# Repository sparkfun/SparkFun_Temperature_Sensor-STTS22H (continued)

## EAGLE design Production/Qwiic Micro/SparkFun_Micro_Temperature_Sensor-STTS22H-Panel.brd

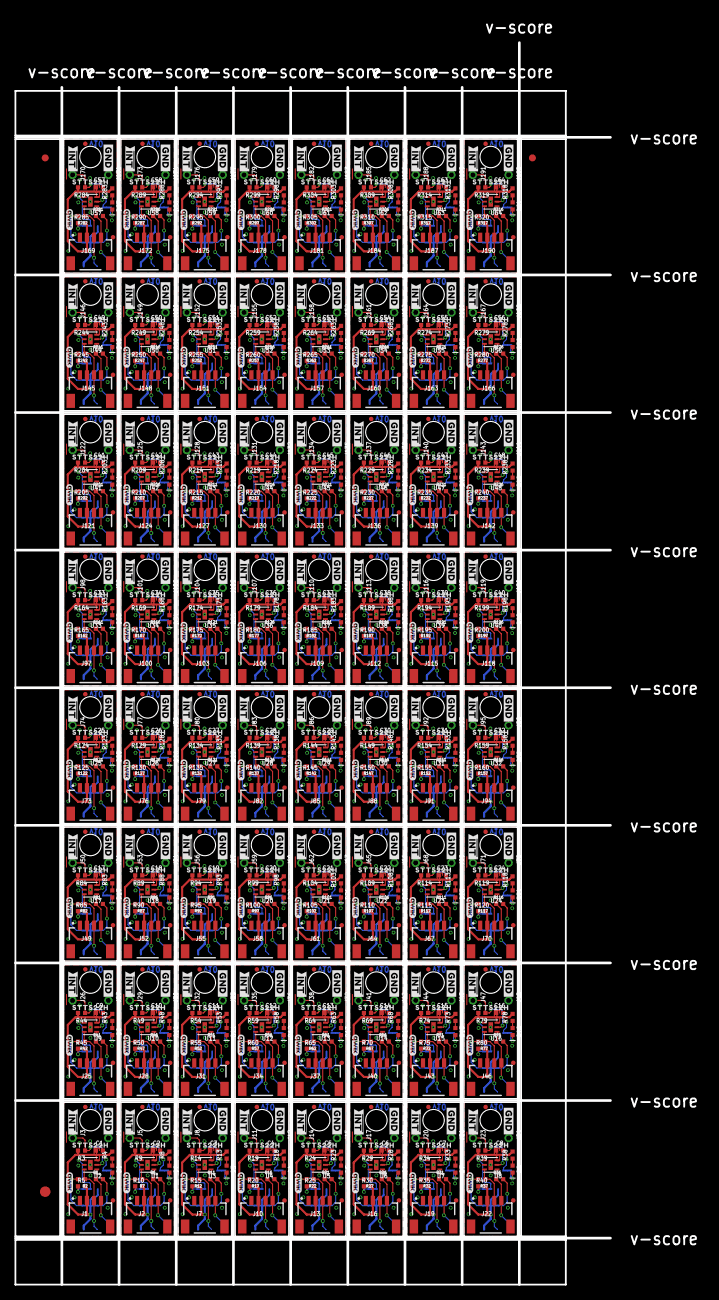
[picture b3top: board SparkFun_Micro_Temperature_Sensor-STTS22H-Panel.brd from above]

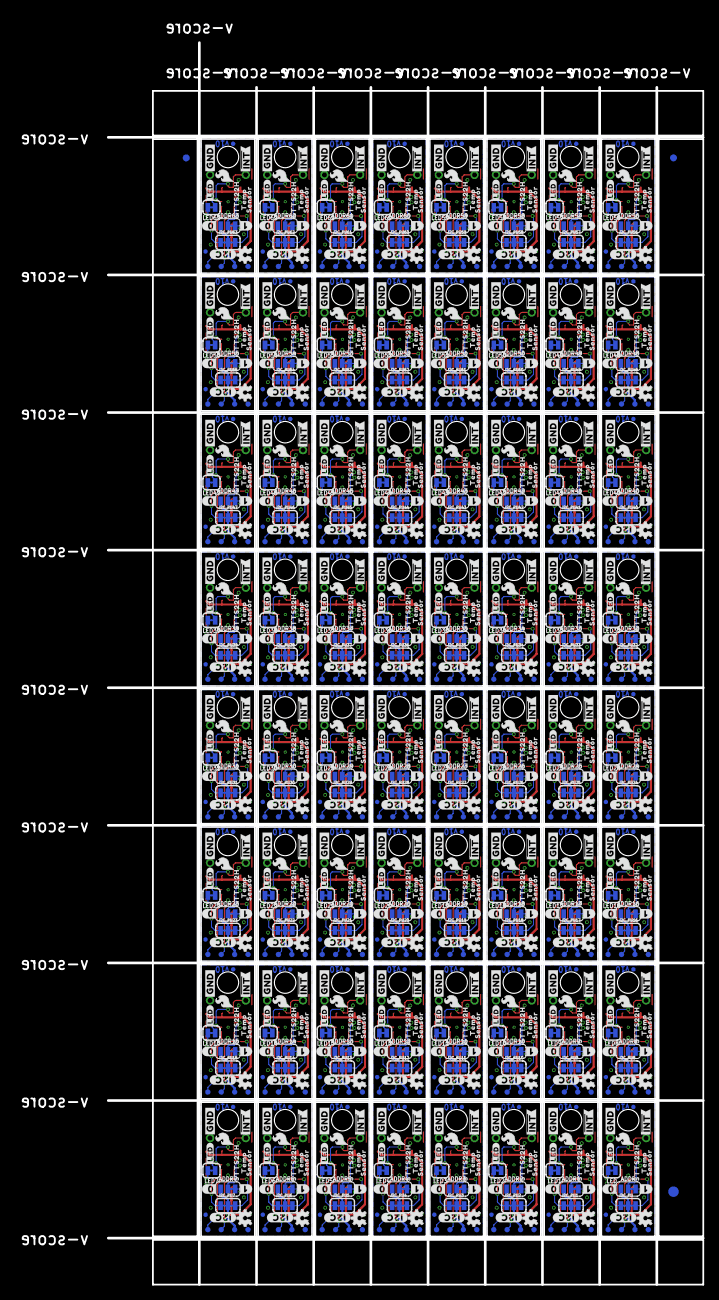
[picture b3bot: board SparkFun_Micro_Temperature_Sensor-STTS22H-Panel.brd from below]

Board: 2 copper layers, 84.6 x 176.5 mm, 2502 parts (1283 on the bottom side), 704 nets.

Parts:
ADDR, ADDR1, ADDR2, ADDR3, ADDR4, ADDR5, ADDR6, ADDR7, ADDR8, ADDR9, ADDR10, ADDR11, ADDR12, ADDR13, ADDR14, ADDR15, ADDR16, ADDR17, ADDR18, ADDR19, ADDR20, ADDR21, ADDR22, ADDR23, ADDR24, ADDR25, ADDR26, ADDR27, ADDR28, ADDR29, ADDR30, ADDR31, ADDR32, ADDR33, ADDR34, ADDR35, ADDR36, ADDR37, ADDR38, ADDR39, ADDR40, ADDR41, ADDR42, ADDR43, ADDR44, ADDR45, ADDR46, ADDR47, ADDR48, ADDR49, ADDR50, ADDR51, ADDR52, ADDR53, ADDR54, ADDR55, ADDR56, ADDR57, ADDR58, ADDR59, ADDR60, ADDR61, ADDR62, ADDR63: JUMPER-SMT_3_1-NC_TRACE_SILK; SMT-JUMPER_3_1-NC_TRACE_SILK
C1, C2, C3, C4, C5, C6, C7, C8, C9, C10, C11, C12, C13, C14, C15, C16, C17, C18, C19, C20, C21, C22, C23, C24, C25, C26, C27, C28, C29, C30, C31, C32, C33, C34, C35, C36, C37, C38, C39, C40, C41, C42, C43, C44, C45, C46, C47, C48, C49, C50, C51, C52, C53, C54, C55, C56, C57, C58, C59, C60, C61, C62, C63, C64: 0.1uF; 0402-TIGHT
D1, D2, D3, D4, D5, D6, D7, D8, D9, D10, D11, D12, D13, D14, D15, D16, D17, D18, D19, D20, D21, D22, D23, D24, D25, D26, D27, D28, D29, D30, D31, D32, D33, D34, D35, D36, D37, D38, D39, D40, D41, D42, D43, D44, D45, D46, D47, D48, D49, D50, D51, D52, D53, D54, D55, D56, D57, D58, D59, D60, D61, D62, D63, D64: RED; LED-0402
E$1, E$2, E$3, E$4: FIDUCIAL-1X2
E$5, E$6: FIDUCIAL-1.5X3
FD1, FD2, FD3, FD4, FD5, FD6, FD7, FD8, FD9, FD10, FD11, FD12, FD13, FD14, FD15, FD16, FD17, FD18, FD19, FD20, FD21, FD22, FD23, FD24, FD25, FD26, FD27, FD28, FD29, FD30, FD31, FD32, FD33, FD34, FD35, FD36, FD37, FD38, FD39, FD40, FD41, FD42, FD43, FD44, FD45, FD46, FD47, FD48, FD49, FD50, FD51, FD52, FD53, FD54, FD55, FD56, FD57, FD58, FD59, FD60, FD61, FD62, FD63, FD64, FD65, FD66, FD67, FD68, FD69, FD70, FD71, FD72, FD73, FD74, FD75, FD76, FD77, FD78, FD79, FD80, FD81, FD82, FD83, FD84, FD85, FD86, FD87, FD88, FD89, FD90, FD91, FD92, FD93, FD94, FD95, FD96, FD97, FD98, FD99, FD100, FD101, FD102, FD103, FD104, FD105, FD106, FD107, FD108, FD109, FD110, FD111, FD112, FD113, FD114, FD115, FD116, FD117, FD118, FD119, FD120, FD121, FD122, FD123, FD124, FD125, FD126, FD127, FD128: FIDUCIALUFIDUCIAL; FIDUCIAL-MICRO
FID1, FID2, FID3, FID4, FID5, FID6, FID7, FID8, FID9, FID10, FID11, FID12, FID13, FID14, FID15, FID16, FID17, FID18, FID19, FID20, FID21, FID22, FID23, FID24, FID25, FID26, FID27, FID28, FID29, FID30, FID31, FID32, FID33, FID34, FID35, FID36, FID37, FID38, FID39, FID40, FID41, FID42, FID43, FID44, FID45, FID46, FID47, FID48, FID49, FID50, FID51, FID52, FID53, FID54, FID55, FID56, FID57, FID58, FID59, FID60, FID61, FID62, FID63, FID64, FID65, FID66, FID67, FID68, FID69, FID70, FID71, FID72, FID73, FID74, FID75, FID76, FID77, FID78, FID79, FID80, FID81, FID82, FID83, FID84, FID85, FID86, FID87, FID88, FID89, FID90, FID91, FID92, FID93, FID94, FID95, FID96, FID97, FID98, FID99, FID100, FID101, FID102, FID103, FID104, FID105, FID106, FID107, FID108, FID109, FID110, FID111, FID112, FID113, FID114, FID115, FID116, FID117, FID118, FID119, FID120, FID121, FID122, FID123, FID124, FID125, FID126, FID127, FID128: FIDUCIALUFIDUCIAL; FIDUCIAL-MICRO
I2C_PU, I2C_PU1, I2C_PU2, I2C_PU3, I2C_PU4, I2C_PU5, I2C_PU6, I2C_PU7, I2C_PU8, I2C_PU9, I2C_PU10, I2C_PU11, I2C_PU12, I2C_PU13, I2C_PU14, I2C_PU15, I2C_PU16, I2C_PU17, I2C_PU18, I2C_PU19, I2C_PU20, I2C_PU21, I2C_PU22, I2C_PU23, I2C_PU24, I2C_PU25, I2C_PU26, I2C_PU27, I2C_PU28, I2C_PU29, I2C_PU30, I2C_PU31, I2C_PU32, I2C_PU33, I2C_PU34, I2C_PU35, I2C_PU36, I2C_PU37, I2C_PU38, I2C_PU39, I2C_PU40, I2C_PU41, I2C_PU42, I2C_PU43, I2C_PU44, I2C_PU45, I2C_PU46, I2C_PU47, I2C_PU48, I2C_PU49, I2C_PU50, I2C_PU51, I2C_PU52, I2C_PU53, I2C_PU54, I2C_PU55, I2C_PU56, I2C_PU57, I2C_PU58, I2C_PU59, I2C_PU60, I2C_PU61, I2C_PU62, I2C_PU63: S_MODE; SMT-JUMPER_3_2-NC_TRACE_SILK
J1, J2, J7, J10, J13, J16, J19, J22, J25, J28, J31, J34, J37, J40, J43, J46, J49, J52, J55, J58, J61, J64, J67, J70, J73, J76, J79, J82, J85, J88, J91, J94, J97, J100, J103, J106, J109, J112, J115, J118, J121, J124, J127, J130, J133, J136, J139, J142, J145, J148, J151, J154, J157, J160, J163, J166, J169, J172, J175, J178, J181, J184, J187, J190: Qwiic Right Angle; JST04_1MM_RA
J3, J4, J5, J6, J8, J9, J11, J12, J14, J15, J17, J18, J20, J21, J23, J24, J26, J27, J29, J30, J32, J33, J35, J36, J38, J39, J41, J42, J44, J45, J47, J48, J50, J51, J53, J54, J56, J57, J59, J60, J62, J63, J65, J66, J68, J69, J71, J72, J74, J75, J77, J78, J80, J81, J83, J84, J86, J87, J89, J90, J92, J93, J95, J96, J98, J99, J101, J102, J104, J105, J107, J108, J110, J111, J113, J114, J116, J117, J119, J120, J122, J123, J125, J126, J128, J129, J131, J132, J134, J135, J137, J138, J140, J141, J143, J144, J146, J147, J149, J150, J152, J153, J155, J156, J158, J159, J161, J162, J164, J165, J167, J168, J170, J171, J173, J174, J176, J177, J179, J180, J182, J183, J185, J186, J188, J189, J191, J192: 1X01_1MM_NO_SILK
LED, LED1, LED2, LED3, LED4, LED5, LED6, LED7, LED8, LED9, LED10, LED11, LED12, LED13, LED14, LED15, LED16, LED17, LED18, LED19, LED20, LED21, LED22, LED23, LED24, LED25, LED26, LED27, LED28, LED29, LED30, LED31, LED32, LED33, LED34, LED35, LED36, LED37, LED38, LED39, LED40, LED41, LED42, LED43, LED44, LED45, LED46, LED47, LED48, LED49, LED50, LED51, LED52, LED53, LED54, LED55, LED56, LED57, LED58, LED59, LED60, LED61, LED62, LED63: JUMPER-SMT_2_NC_TRACE_SILK; SMT-JUMPER_2_NC_TRACE_SILK
LOGO1, LOGO5, LOGO8, LOGO11, LOGO14, LOGO17, LOGO20, LOGO23, LOGO26, LOGO29, LOGO32, LOGO35, LOGO38, LOGO41, LOGO44, LOGO47, LOGO50, LOGO53, LOGO56, LOGO59, LOGO62, LOGO65, LOGO68, LOGO71, LOGO74, LOGO77, LOGO80, LOGO83, LOGO86, LOGO89, LOGO92, LOGO95, LOGO98, LOGO101, LOGO104, LOGO107, LOGO110, LOGO113, LOGO116, LOGO119, LOGO122, LOGO125, LOGO128, LOGO131, LOGO134, LOGO137, LOGO140, LOGO143, LOGO146, LOGO149, LOGO152, LOGO155, LOGO158, LOGO161, LOGO164, LOGO167, LOGO170, LOGO173, LOGO176, LOGO179, LOGO182, LOGO185, LOGO188, LOGO191: QWIIC_LOGO_3MM; QWIIC_3MM
LOGO2, LOGO4, LOGO7, LOGO10, LOGO13, LOGO16, LOGO19, LOGO22, LOGO25, LOGO28, LOGO31, LOGO34, LOGO37, LOGO40, LOGO43, LOGO46, LOGO49, LOGO52, LOGO55, LOGO58, LOGO61, LOGO64, LOGO67, LOGO70, LOGO73, LOGO76, LOGO79, LOGO82, LOGO85, LOGO88, LOGO91, LOGO94, LOGO97, LOGO100, LOGO103, LOGO106, LOGO109, LOGO112, LOGO115, LOGO118, LOGO121, LOGO124, LOGO127, LOGO130, LOGO133, LOGO136, LOGO139, LOGO142, LOGO145, LOGO148, LOGO151, LOGO154, LOGO157, LOGO160, LOGO163, LOGO166, LOGO169, LOGO172, LOGO175, LOGO178, LOGO181, LOGO184, LOGO187, LOGO190: OSHW-LOGOMINI; OSHW-LOGO-MINI
LOGO3, LOGO6, LOGO9, LOGO12, LOGO15, LOGO18, LOGO21, LOGO24, LOGO27, LOGO30, LOGO33, LOGO36, LOGO39, LOGO42, LOGO45, LOGO48, LOGO51, LOGO54, LOGO57, LOGO60, LOGO63, LOGO66, LOGO69, LOGO72, LOGO75, LOGO78, LOGO81, LOGO84, LOGO87, LOGO90, LOGO93, LOGO96, LOGO99, LOGO102, LOGO105, LOGO108, LOGO111, LOGO114, LOGO117, LOGO120, LOGO123, LOGO126, LOGO129, LOGO132, LOGO135, LOGO138, LOGO141, LOGO144, LOGO147, LOGO150, LOGO153, LOGO156, LOGO159, LOGO162, LOGO165, LOGO168, LOGO171, LOGO174, LOGO177, LOGO180, LOGO183, LOGO186, LOGO189, LOGO192: SFE_LOGO_NAME_FLAMEBLANK; BLANK
R1, R2, R4, R6, R7, R8, R11, R12, R13, R16, R17, R18, R21, R22, R23, R26, R27, R28, R31, R32, R33, R36, R37, R38, R41, R42, R43, R46, R47, R48, R51, R52, R53, R56, R57, R58, R61, R62, R63, R66, R67, R68, R71, R72, R73, R76, R77, R78, R81, R82, R83, R86, R87, R88, R91, R92, R93, R96, R97, R98, R101, R102, R103, R106, R107, R108, R111, R112, R113, R116, R117, R118, R121, R122, R123, R126, R127, R128, R131, R132, R133, R136, R137, R138, R141, R142, R143, R146, R147, R148, R151, R152, R153, R156, R157, R158, R161, R162, R163, R166, R167, R168, R171, R172, R173, R176, R177, R178, R181, R182, R183, R186, R187, R188, R191, R192, R193, R196, R197, R198, R201, R202, R203, R206, R207, R208, R211, R212, R213, R216, R217, R218, R221, R222, R223, R226, R227, R228, R231, R232, R233, R236, R237, R238, R241, R242, R243, R246, R247, R248, R251, R252, R253, R256, R257, R258, R261, R262, R263, R266, R267, R268, R271, R272, R273, R276, R277, R278, R281, R282, R283, R286, R287, R288, R291, R292, R293, R296, R297, R298, R301, R302, R303, R306, R307, R308, R311, R312, R313, R316, R317, R318: 2.2k; 0402-TIGHT
R3, R9, R14, R19, R24, R29, R34, R39, R44, R49, R54, R59, R64, R69, R74, R79, R84, R89, R94, R99, R104, R109, R114, R119, R124, R129, R134, R139, R144, R149, R154, R159, R164, R169, R174, R179, R184, R189, R194, R199, R204, R209, R214, R219, R224, R229, R234, R239, R244, R249, R254, R259, R264, R269, R274, R279, R284, R289, R294, R299, R304, R309, R314, R319: 10k; 0402-TIGHT
R5, R10, R15, R20, R25, R30, R35, R40, R45, R50, R55, R60, R65, R70, R75, R80, R85, R90, R95, R100, R105, R110, R115, R120, R125, R130, R135, R140, R145, R150, R155, R160, R165, R170, R175, R180, R185, R190, R195, R200, R205, R210, R215, R220, R225, R230, R235, R240, R245, R250, R255, R260, R265, R270, R275, R280, R285, R290, R295, R300, R305, R310, R315, R320: 15K; 0402-TIGHT
STANDOFF1, STANDOFF2, STANDOFF3, STANDOFF4, STANDOFF5, STANDOFF6, STANDOFF7, STANDOFF8, STANDOFF9, STANDOFF10, STANDOFF11, STANDOFF12, STANDOFF13, STANDOFF14, STANDOFF15, STANDOFF16, STANDOFF17, STANDOFF18, STANDOFF19, STANDOFF20, STANDOFF21, STANDOFF22, STANDOFF23, STANDOFF24, STANDOFF25, STANDOFF26, STANDOFF27, STANDOFF28, STANDOFF29, STANDOFF30, STANDOFF31, STANDOFF32, STANDOFF33, STANDOFF34, STANDOFF35, STANDOFF36, STANDOFF37, STANDOFF38, STANDOFF39, STANDOFF40, STANDOFF41, STANDOFF42, STANDOFF43, STANDOFF44, STANDOFF45, STANDOFF46, STANDOFF47, STANDOFF48, STANDOFF49, STANDOFF50, STANDOFF51, STANDOFF52, STANDOFF53, STANDOFF54, STANDOFF55, STANDOFF56, STANDOFF57, STANDOFF58, STANDOFF59, STANDOFF60, STANDOFF61, STANDOFF62, STANDOFF63, STANDOFF64: STAND-OFFTIGHT; STAND-OFF-TIGHT
TP1, TP2, TP3, TP4, TP5, TP6, TP7, TP8, TP9, TP10, TP11, TP12, TP13, TP14, TP15, TP16, TP17, TP18, TP19, TP20, TP21, TP22, TP23, TP24, TP25, TP26, TP27, TP28, TP29, TP30, TP31, TP32, TP33, TP34, TP35, TP36, TP37, TP38, TP39, TP40, TP41, TP42, TP43, TP44, TP45, TP46, TP47, TP48, TP49, TP50, TP51, TP52, TP53, TP54, TP55, TP56, TP57, TP58, TP59, TP60, TP61, TP62, TP63, TP64, TP65, TP66, TP67, TP68, TP69, TP70, TP71, TP72, TP73, TP74, TP75, TP76, TP77, TP78, TP79, TP80, TP81, TP82, TP83, TP84, TP85, TP86, TP87, TP88, TP89, TP90, TP91, TP92, TP93, TP94, TP95, TP96, TP97, TP98, TP99, TP100, TP101, TP102, TP103, TP104, TP105, TP106, TP107, TP108, TP109, TP110, TP111, TP112, TP113, TP114, TP115, TP116, TP117, TP118, TP119, TP120, TP121, TP122, TP123, TP124, TP125, TP126, TP127, TP128, TP129, TP130, TP131, TP132, TP133, TP134, TP135, TP136, TP137, TP138, TP139, TP140, TP141, TP142, TP143, TP144, TP145, TP146, TP147, TP148, TP149, TP150, TP151, TP152, TP153, TP154, TP155, TP156, TP157, TP158, TP159, TP160, TP161, TP162, TP163, TP164, TP165, TP166, TP167, TP168, TP169, TP170, TP171, TP172, TP173, TP174, TP175, TP176, TP177, TP178, TP179, TP180, TP181, TP182, TP183, TP184, TP185, TP186, TP187, TP188, TP189, TP190, TP191, TP192, TP193, TP194, TP195, TP196, TP197, TP198, TP199, TP200, TP201, TP202, TP203, TP204, TP205, TP206, TP207, TP208, TP209, TP210, TP211, TP212, TP213, TP214, TP215, TP216, TP217, TP218, TP219, TP220, TP221, TP222, TP223, TP224, TP225, TP226, TP227, TP228, TP229, TP230, TP231, TP232, TP233, TP234, TP235, TP236, TP237, TP238, TP239, TP240, TP241, TP242, TP243, TP244, TP245, TP246, TP247, TP248, TP249, TP250, TP251, TP252, TP253, TP254, TP255, TP256: TEST-POINT3; PAD.03X.03
U1, U2, U3, U4, U5, U6, U7, U8, U9, U10, U11, U12, U13, U14, U15, U16, U17, U18, U19, U20, U21, U22, U23, U24, U25, U26, U27, U28, U29, U30, U31, U32, U33, U34, U35, U36, U37, U38, U39, U40, U41, U42, U43, U44, U45, U46, U47, U48, U49, U50, U51, U52, U53, U54, U55, U56, U57, U58, U59, U60, U61, U62, U63, U64: STTS22H; UDFN-6L
U$1, U$15, U$28, U$42, U$55, U$68, U$81, U$94, U$107, U$120, U$133, U$146, U$159, U$172, U$185, U$198, U$211, U$224, U$237, U$250, U$263, U$276, U$289, U$302, U$315, U$328, U$341, U$354, U$367, U$380, U$393, U$406, U$419, U$432, U$445, U$458, U$471, U$484, U$497, U$510, U$523, U$536, U$549, U$562, U$575, U$588, U$601, U$614, U$627, U$640, U$653, U$666, U$679, U$692, U$705, U$718, U$731, U$744, U$757, U$770, U$783, U$796, U$809, U$822: #0#4
U$2, U$16, U$30, U$43, U$56, U$69, U$82, U$95, U$108, U$121, U$134, U$147, U$160, U$173, U$186, U$199, U$212, U$225, U$238, U$251, U$264, U$277, U$290, U$303, U$316, U$329, U$342, U$355, U$368, U$381, U$394, U$407, U$420, U$433, U$446, U$459, U$472, U$485, U$498, U$511, U$524, U$537, U$550, U$563, U$576, U$589, U$602, U$615, U$628, U$641, U$654, U$667, U$680, U$693, U$706, U$719, U$732, U$745, U$758, U$771, U$784, U$797, U$810, U$823: #1#4
U$3, U$14, U$27, U$41, U$54, U$67, U$80, U$93, U$106, U$119, U$132, U$145, U$158, U$171, U$184, U$197, U$210, U$223, U$236, U$249, U$262, U$275, U$288, U$301, U$314, U$327, U$340, U$353, U$366, U$379, U$392, U$405, U$418, U$431, U$444, U$457, U$470, U$483, U$496, U$509, U$522, U$535, U$548, U$561, U$574, U$587, U$600, U$613, U$626, U$639, U$652, U$665, U$678, U$691, U$704, U$717, U$730, U$743, U$756, U$769, U$782, U$795, U$808, U$821: #LED#2121
U$4, U$10, U$18, U$19, U$32, U$33, U$45, U$46, U$58, U$59, U$71, U$72, U$84, U$85, U$97, U$98, U$110, U$111, U$123, U$124, U$136, U$137, U$149, U$150, U$162, U$163, U$175, U$176, U$188, U$189, U$201, U$202, U$214, U$215, U$227, U$228, U$240, U$241, U$253, U$254, U$266, U$267, U$279, U$280, U$292, U$293, U$305, U$306, U$318, U$319, U$331, U$332, U$344, U$345, U$357, U$358, U$370, U$371, U$383, U$384, U$396, U$397, U$409, U$410, U$422, U$423, U$435, U$436, U$448, U$449, U$461, U$462, U$474, U$475, U$487, U$488, U$500, U$501, U$513, U$514, U$526, U$527, U$539, U$540, U$552, U$553, U$565, U$566, U$578, U$579, U$591, U$592, U$604, U$605, U$617, U$618, U$630, U$631, U$643, U$644, U$656, U$657, U$669, U$670, U$682, U$683, U$695, U$696, U$708, U$709, U$721, U$722, U$734, U$735, U$747, U$748, U$760, U$761, U$773, U$774, U$786, U$787, U$799, U$800, U$812, U$813, U$825, U$826: #GND#4
U$5, U$6, U$20, U$21, U$34, U$35, U$47, U$48, U$60, U$61, U$73, U$74, U$86, U$87, U$99, U$100, U$112, U$113, U$125, U$126, U$138, U$139, U$151, U$152, U$164, U$165, U$177, U$178, U$190, U$191, U$203, U$204, U$216, U$217, U$229, U$230, U$242, U$243, U$255, U$256, U$268, U$269, U$281, U$282, U$294, U$295, U$307, U$308, U$320, U$321, U$333, U$334, U$346, U$347, U$359, U$360, U$372, U$373, U$385, U$386, U$398, U$399, U$411, U$412, U$424, U$425, U$437, U$438, U$450, U$451, U$463, U$464, U$476, U$477, U$489, U$490, U$502, U$503, U$515, U$516, U$528, U$529, U$541, U$542, U$554, U$555, U$567, U$568, U$580, U$581, U$593, U$594, U$606, U$607, U$619, U$620, U$632, U$633, U$645, U$646, U$658, U$659, U$671, U$672, U$684, U$685, U$697, U$698, U$710, U$711, U$723, U$724, U$736, U$737, U$749, U$750, U$762, U$763, U$775, U$776, U$788, U$789, U$801, U$802, U$814, U$815, U$827, U$828: ##INT##9
U$7, U$8, U$22, U$23, U$36, U$37, U$49, U$50, U$62, U$63, U$75, U$76, U$88, U$89, U$101, U$102, U$114, U$115, U$127, U$128, U$140, U$141, U$153, U$154, U$166, U$167, U$179, U$180, U$192, U$193, U$205, U$206, U$218, U$219, U$231, U$232, U$244, U$245, U$257, U$258, U$270, U$271, U$283, U$284, U$296, U$297, U$309, U$310, U$322, U$323, U$335, U$336, U$348, U$349, U$361, U$362, U$374, U$375, U$387, U$388, U$400, U$401, U$413, U$414, U$426, U$427, U$439, U$440, U$452, U$453, U$465, U$466, U$478, U$479, U$491, U$492, U$504, U$505, U$517, U$518, U$530, U$531, U$543, U$544, U$556, U$557, U$569, U$570, U$582, U$583, U$595, U$596, U$608, U$609, U$621, U$622, U$634, U$635, U$647, U$648, U$660, U$661, U$673, U$674, U$686, U$687, U$699, U$700, U$712, U$713, U$725, U$726, U$738, U$739, U$751, U$752, U$764, U$765, U$777, U$778, U$790, U$791, U$803, U$804, U$816, U$817, U$829, U$830: STTS22H11
U$9, U$24, U$38, U$51, U$64, U$77, U$90, U$103, U$116, U$129, U$142, U$155, U$168, U$181, U$194, U$207, U$220, U$233, U$246, U$259, U$272, U$285, U$298, U$311, U$324, U$337, U$350, U$363, U$376, U$389, U$402, U$415, U$428, U$441, U$454, U$467, U$480, U$493, U$506, U$519, U$532, U$545, U$558, U$571, U$584, U$597, U$610, U$623, U$636, U$649, U$662, U$675, U$688, U$701, U$714, U$727, U$740, U$753, U$766, U$779, U$792, U$805, U$818, U$831: TEMP24
U$11, U$25, U$39, U$52, U$65, U$78, U$91, U$104, U$117, U$130, U$143, U$156, U$169, U$182, U$195, U$208, U$221, U$234, U$247, U$260, U$273, U$286, U$299, U$312, U$325, U$338, U$351, U$364, U$377, U$390, U$403, U$416, U$429, U$442, U$455, U$468, U$481, U$494, U$507, U$520, U$533, U$546, U$559, U$572, U$585, U$598, U$611, U$624, U$637, U$650, U$663, U$676, U$689, U$702, U$715, U$728, U$741, U$754, U$767, U$780, U$793, U$806, U$819, U$832: SENSOR25
U$12, U$17, U$31, U$44, U$57, U$70, U$83, U$96, U$109, U$122, U$135, U$148, U$161, U$174, U$187, U$200, U$213, U$226, U$239, U$252, U$265, U$278, U$291, U$304, U$317, U$330, U$343, U$356, U$369, U$382, U$395, U$408, U$421, U$434, U$447, U$460, U$473, U$486, U$499, U$512, U$525, U$538, U$551, U$564, U$577, U$590, U$603, U$616, U$629, U$642, U$655, U$668, U$681, U$694, U$707, U$720, U$733, U$746, U$759, U$772, U$785, U$798, U$811, U$824: #I2C#4
U$13, U$26, U$29, U$40, U$53, U$66, U$79, U$92, U$105, U$118, U$131, U$144, U$157, U$170, U$183, U$196, U$209, U$222, U$235, U$248, U$261, U$274, U$287, U$300, U$313, U$326, U$339, U$352, U$365, U$378, U$391, U$404, U$417, U$430, U$443, U$456, U$469, U$482, U$495, U$508, U$521, U$534, U$547, U$560, U$573, U$586, U$599, U$612, U$625, U$638, U$651, U$664, U$677, U$690, U$703, U$716, U$729, U$742, U$755, U$768, U$781, U$794, U$807, U$820: SFE_LOGO_FLAME_.1

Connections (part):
3.3V: ADDR.1, C1.1, I2C_PU.2, J1.2, R3.2, R4.2, R5.2, TP3.1, U2.P3
3.3V1: ADDR1.1, C2.1, I2C_PU1.2, J2.2, R8.2, R9.2, R10.2, TP7.1, U1.P3
3.3V2: ADDR2.1, C3.1, I2C_PU2.2, J7.2, R13.2, R14.2, R15.2, TP11.1, U3.P3
3.3V3: ADDR3.1, C4.1, I2C_PU3.2, J10.2, R18.2, R19.2, R20.2, TP15.1, U4.P3
3.3V4: ADDR4.1, C5.1, I2C_PU4.2, J13.2, R23.2, R24.2, R25.2, TP19.1, U5.P3
3.3V5: ADDR5.1, C6.1, I2C_PU5.2, J16.2, R28.2, R29.2, R30.2, TP23.1, U6.P3
3.3V6: ADDR6.1, C7.1, I2C_PU6.2, J19.2, R33.2, R34.2, R35.2, TP27.1, U7.P3
3.3V7: ADDR7.1, C8.1, I2C_PU7.2, J22.2, R38.2, R39.2, R40.2, TP31.1, U8.P3
3.3V8: ADDR8.1, C9.1, I2C_PU8.2, J25.2, R43.2, R44.2, R45.2, TP35.1, U9.P3
3.3V9: ADDR9.1, C10.1, I2C_PU9.2, J28.2, R48.2, R49.2, R50.2, TP39.1, U10.P3
3.3V10: ADDR10.1, C11.1, I2C_PU10.2, J31.2, R53.2, R54.2, R55.2, TP43.1, U11.P3
3.3V11: ADDR11.1, C12.1, I2C_PU11.2, J34.2, R58.2, R59.2, R60.2, TP47.1, U12.P3
3.3V12: ADDR12.1, C13.1, I2C_PU12.2, J37.2, R63.2, R64.2, R65.2, TP51.1, U13.P3
3.3V13: ADDR13.1, C14.1, I2C_PU13.2, J40.2, R68.2, R69.2, R70.2, TP55.1, U14.P3
3.3V14: ADDR14.1, C15.1, I2C_PU14.2, J43.2, R73.2, R74.2, R75.2, TP59.1, U15.P3
3.3V15: ADDR15.1, C16.1, I2C_PU15.2, J46.2, R78.2, R79.2, R80.2, TP63.1, U16.P3
3.3V16: ADDR16.1, C17.1, I2C_PU16.2, J49.2, R83.2, R84.2, R85.2, TP67.1, U17.P3
3.3V17: ADDR17.1, C18.1, I2C_PU17.2, J52.2, R88.2, R89.2, R90.2, TP71.1, U18.P3
3.3V18: ADDR18.1, C19.1, I2C_PU18.2, J55.2, R93.2, R94.2, R95.2, TP75.1, U19.P3
3.3V19: ADDR19.1, C20.1, I2C_PU19.2, J58.2, R98.2, R99.2, R100.2, TP79.1, U20.P3
3.3V20: ADDR20.1, C21.1, I2C_PU20.2, J61.2, R103.2, R104.2, R105.2, TP83.1, U21.P3
3.3V21: ADDR21.1, C22.1, I2C_PU21.2, J64.2, R108.2, R109.2, R110.2, TP87.1, U22.P3
3.3V22: ADDR22.1, C23.1, I2C_PU22.2, J67.2, R113.2, R114.2, R115.2, TP91.1, U23.P3
3.3V23: ADDR23.1, C24.1, I2C_PU23.2, J70.2, R118.2, R119.2, R120.2, TP95.1, U24.P3
3.3V24: ADDR24.1, C25.1, I2C_PU24.2, J73.2, R123.2, R124.2, R125.2, TP99.1, U25.P3
3.3V25: ADDR25.1, C26.1, I2C_PU25.2, J76.2, R128.2, R129.2, R130.2, TP103.1, U26.P3
3.3V26: ADDR26.1, C27.1, I2C_PU26.2, J79.2, R133.2, R134.2, R135.2, TP107.1, U27.P3
3.3V27: ADDR27.1, C28.1, I2C_PU27.2, J82.2, R138.2, R139.2, R140.2, TP111.1, U28.P3
3.3V28: ADDR28.1, C29.1, I2C_PU28.2, J85.2, R143.2, R144.2, R145.2, TP115.1, U29.P3
3.3V29: ADDR29.1, C30.1, I2C_PU29.2, J88.2, R148.2, R149.2, R150.2, TP119.1, U30.P3
3.3V30: ADDR30.1, C31.1, I2C_PU30.2, J91.2, R153.2, R154.2, R155.2, TP123.1, U31.P3
3.3V31: ADDR31.1, C32.1, I2C_PU31.2, J94.2, R158.2, R159.2, R160.2, TP127.1, U32.P3
3.3V32: ADDR32.1, C33.1, I2C_PU32.2, J97.2, R163.2, R164.2, R165.2, TP131.1, U33.P3
3.3V33: ADDR33.1, C34.1, I2C_PU33.2, J100.2, R168.2, R169.2, R170.2, TP135.1, U34.P3
3.3V34: ADDR34.1, C35.1, I2C_PU34.2, J103.2, R173.2, R174.2, R175.2, TP139.1, U35.P3
3.3V35: ADDR35.1, C36.1, I2C_PU35.2, J106.2, R178.2, R179.2, R180.2, TP143.1, U36.P3
3.3V36: ADDR36.1, C37.1, I2C_PU36.2, J109.2, R183.2, R184.2, R185.2, TP147.1, U37.P3
3.3V37: ADDR37.1, C38.1, I2C_PU37.2, J112.2, R188.2, R189.2, R190.2, TP151.1, U38.P3
3.3V38: ADDR38.1, C39.1, I2C_PU38.2, J115.2, R193.2, R194.2, R195.2, TP155.1, U39.P3
3.3V39: ADDR39.1, C40.1, I2C_PU39.2, J118.2, R198.2, R199.2, R200.2, TP159.1, U40.P3
3.3V40: ADDR40.1, C41.1, I2C_PU40.2, J121.2, R203.2, R204.2, R205.2, TP163.1, U41.P3
3.3V41: ADDR41.1, C42.1, I2C_PU41.2, J124.2, R208.2, R209.2, R210.2, TP167.1, U42.P3
3.3V42: ADDR42.1, C43.1, I2C_PU42.2, J127.2, R213.2, R214.2, R215.2, TP171.1, U43.P3
3.3V43: ADDR43.1, C44.1, I2C_PU43.2, J130.2, R218.2, R219.2, R220.2, TP175.1, U44.P3
3.3V44: ADDR44.1, C45.1, I2C_PU44.2, J133.2, R223.2, R224.2, R225.2, TP179.1, U45.P3
3.3V45: ADDR45.1, C46.1, I2C_PU45.2, J136.2, R228.2, R229.2, R230.2, TP183.1, U46.P3
3.3V46: ADDR46.1, C47.1, I2C_PU46.2, J139.2, R233.2, R234.2, R235.2, TP187.1, U47.P3
3.3V47: ADDR47.1, C48.1, I2C_PU47.2, J142.2, R238.2, R239.2, R240.2, TP191.1, U48.P3
3.3V48: ADDR48.1, C49.1, I2C_PU48.2, J145.2, R243.2, R244.2, R245.2, TP195.1, U49.P3
3.3V49: ADDR49.1, C50.1, I2C_PU49.2, J148.2, R248.2, R249.2, R250.2, TP199.1, U50.P3
3.3V50: ADDR50.1, C51.1, I2C_PU50.2, J151.2, R253.2, R254.2, R255.2, TP203.1, U51.P3
3.3V51: ADDR51.1, C52.1, I2C_PU51.2, J154.2, R258.2, R259.2, R260.2, TP207.1, U52.P3
3.3V52: ADDR52.1, C53.1, I2C_PU52.2, J157.2, R263.2, R264.2, R265.2, TP211.1, U53.P3
3.3V53: ADDR53.1, C54.1, I2C_PU53.2, J160.2, R268.2, R269.2, R270.2, TP215.1, U54.P3
3.3V54: ADDR54.1, C55.1, I2C_PU54.2, J163.2, R273.2, R274.2, R275.2, TP219.1, U55.P3
3.3V55: ADDR55.1, C56.1, I2C_PU55.2, J166.2, R278.2, R279.2, R280.2, TP223.1, U56.P3
3.3V56: ADDR56.1, C57.1, I2C_PU56.2, J169.2, R283.2, R284.2, R285.2, TP227.1, U57.P3
3.3V57: ADDR57.1, C58.1, I2C_PU57.2, J172.2, R288.2, R289.2, R290.2, TP231.1, U58.P3
3.3V58: ADDR58.1, C59.1, I2C_PU58.2, J175.2, R293.2, R294.2, R295.2, TP235.1, U59.P3
3.3V59: ADDR59.1, C60.1, I2C_PU59.2, J178.2, R298.2, R299.2, R300.2, TP239.1, U60.P3
3.3V60: ADDR60.1, C61.1, I2C_PU60.2, J181.2, R303.2, R304.2, R305.2, TP243.1, U61.P3
3.3V61: ADDR61.1, C62.1, I2C_PU61.2, J184.2, R308.2, R309.2, R310.2, TP247.1, U62.P3
3.3V62: ADDR62.1, C63.1, I2C_PU62.2, J187.2, R313.2, R314.2, R315.2, TP251.1, U63.P3
3.3V63: ADDR63.1, C64.1, I2C_PU63.2, J190.2, R318.2, R319.2, R320.2, TP255.1, U64.P3
!INT!: J3.1, R3.1, U2.P2
!INT!1: J5.1, R9.1, U1.P2
!INT!2: J8.1, R14.1, U3.P2
!INT!3: J11.1, R19.1, U4.P2
!INT!4: J14.1, R24.1, U5.P2
!INT!5: J17.1, R29.1, U6.P2
!INT!6: J20.1, R34.1, U7.P2
!INT!7: J23.1, R39.1, U8.P2
!INT!8: J26.1, R44.1, U9.P2
!INT!9: J29.1, R49.1, U10.P2
!INT!10: J32.1, R54.1, U11.P2
!INT!11: J35.1, R59.1, U12.P2
!INT!12: J38.1, R64.1, U13.P2
!INT!13: J41.1, R69.1, U14.P2
!INT!14: J44.1, R74.1, U15.P2
!INT!15: J47.1, R79.1, U16.P2
!INT!16: J50.1, R84.1, U17.P2
!INT!17: J53.1, R89.1, U18.P2
!INT!18: J56.1, R94.1, U19.P2
!INT!19: J59.1, R99.1, U20.P2
!INT!20: J62.1, R104.1, U21.P2
!INT!21: J65.1, R109.1, U22.P2
!INT!22: J68.1, R114.1, U23.P2
!INT!23: J71.1, R119.1, U24.P2
!INT!24: J74.1, R124.1, U25.P2
!INT!25: J77.1, R129.1, U26.P2
!INT!26: J80.1, R134.1, U27.P2
!INT!27: J83.1, R139.1, U28.P2
!INT!28: J86.1, R144.1, U29.P2
!INT!29: J89.1, R149.1, U30.P2
!INT!30: J92.1, R154.1, U31.P2
!INT!31: J95.1, R159.1, U32.P2
!INT!32: J98.1, R164.1, U33.P2
!INT!33: J101.1, R169.1, U34.P2
!INT!34: J104.1, R174.1, U35.P2
!INT!35: J107.1, R179.1, U36.P2
!INT!36: J110.1, R184.1, U37.P2
!INT!37: J113.1, R189.1, U38.P2
!INT!38: J116.1, R194.1, U39.P2
!INT!39: J119.1, R199.1, U40.P2
!INT!40: J122.1, R204.1, U41.P2
!INT!41: J125.1, R209.1, U42.P2
!INT!42: J128.1, R214.1, U43.P2
!INT!43: J131.1, R219.1, U44.P2
!INT!44: J134.1, R224.1, U45.P2
!INT!45: J137.1, R229.1, U46.P2
!INT!46: J140.1, R234.1, U47.P2
!INT!47: J143.1, R239.1, U48.P2
!INT!48: J146.1, R244.1, U49.P2
!INT!49: J149.1, R249.1, U50.P2
!INT!50: J152.1, R254.1, U51.P2
!INT!51: J155.1, R259.1, U52.P2
!INT!52: J158.1, R264.1, U53.P2
!INT!53: J161.1, R269.1, U54.P2
!INT!54: J164.1, R274.1, U55.P2
!INT!55: J167.1, R279.1, U56.P2
!INT!56: J170.1, R284.1, U57.P2
!INT!57: J173.1, R289.1, U58.P2
!INT!58: J176.1, R294.1, U59.P2
!INT!59: J179.1, R299.1, U60.P2
!INT!60: J182.1, R304.1, U61.P2
!INT!61: J185.1, R309.1, U62.P2
!INT!62: J188.1, R314.1, U63.P2
!INT!63: J191.1, R319.1, U64.P2
ADDR: ADDR.2, U2.P4
ADDR1: ADDR1.2, U1.P4
ADDR2: ADDR2.2, U3.P4
ADDR3: ADDR3.2, U4.P4
ADDR4: ADDR4.2, U5.P4
ADDR5: ADDR5.2, U6.P4
ADDR6: ADDR6.2, U7.P4
ADDR7: ADDR7.2, U8.P4
ADDR8: ADDR8.2, U9.P4
ADDR9: ADDR9.2, U10.P4
ADDR10: ADDR10.2, U11.P4
ADDR11: ADDR11.2, U12.P4
ADDR12: ADDR12.2, U13.P4
ADDR13: ADDR13.2, U14.P4
ADDR14: ADDR14.2, U15.P4
ADDR15: ADDR15.2, U16.P4
ADDR16: ADDR16.2, U17.P4
ADDR17: ADDR17.2, U18.P4
ADDR18: ADDR18.2, U19.P4
ADDR19: ADDR19.2, U20.P4
ADDR20: ADDR20.2, U21.P4
ADDR21: ADDR21.2, U22.P4
ADDR22: ADDR22.2, U23.P4
ADDR23: ADDR23.2, U24.P4
ADDR24: ADDR24.2, U25.P4
ADDR25: ADDR25.2, U26.P4
ADDR26: ADDR26.2, U27.P4
ADDR27: ADDR27.2, U28.P4
ADDR28: ADDR28.2, U29.P4
ADDR29: ADDR29.2, U30.P4
ADDR30: ADDR30.2, U31.P4
ADDR31: ADDR31.2, U32.P4
ADDR32: ADDR32.2, U33.P4
ADDR33: ADDR33.2, U34.P4
ADDR34: ADDR34.2, U35.P4
ADDR35: ADDR35.2, U36.P4
ADDR36: ADDR36.2, U37.P4
ADDR37: ADDR37.2, U38.P4
ADDR38: ADDR38.2, U39.P4
ADDR39: ADDR39.2, U40.P4
ADDR40: ADDR40.2, U41.P4
ADDR41: ADDR41.2, U42.P4
ADDR42: ADDR42.2, U43.P4
ADDR43: ADDR43.2, U44.P4
ADDR44: ADDR44.2, U45.P4
ADDR45: ADDR45.2, U46.P4
ADDR46: ADDR46.2, U47.P4
ADDR47: ADDR47.2, U48.P4
ADDR48: ADDR48.2, U49.P4
ADDR49: ADDR49.2, U50.P4
ADDR50: ADDR50.2, U51.P4
ADDR51: ADDR51.2, U52.P4
ADDR52: ADDR52.2, U53.P4
ADDR53: ADDR53.2, U54.P4
ADDR54: ADDR54.2, U55.P4
ADDR55: ADDR55.2, U56.P4
ADDR56: ADDR56.2, U57.P4
ADDR57: ADDR57.2, U58.P4
ADDR58: ADDR58.2, U59.P4
ADDR59: ADDR59.2, U60.P4
ADDR60: ADDR60.2, U61.P4
ADDR61: ADDR61.2, U62.P4
ADDR62: ADDR62.2, U63.P4
ADDR63: ADDR63.2, U64.P4
GND: C1.2, J1.1, J4.1, LED.1, TP4.1, U2.P5, U2.P7
GND1: C2.2, J2.1, J6.1, LED1.1, TP8.1, U1.P5, U1.P7
GND2: C3.2, J7.1, J9.1, LED2.1, TP12.1, U3.P5, U3.P7
GND3: C4.2, J10.1, J12.1, LED3.1, TP16.1, U4.P5, U4.P7
GND4: C5.2, J13.1, J15.1, LED4.1, TP20.1, U5.P5, U5.P7
GND5: C6.2, J16.1, J18.1, LED5.1, TP24.1, U6.P5, U6.P7
GND6: C7.2, J19.1, J21.1, LED6.1, TP28.1, U7.P5, U7.P7
GND7: C8.2, J22.1, J24.1, LED7.1, TP32.1, U8.P5, U8.P7
GND8: C9.2, J25.1, J27.1, LED8.1, TP36.1, U9.P5, U9.P7
GND9: C10.2, J28.1, J30.1, LED9.1, TP40.1, U10.P5, U10.P7
GND10: C11.2, J31.1, J33.1, LED10.1, TP44.1, U11.P5, U11.P7
GND11: C12.2, J34.1, J36.1, LED11.1, TP48.1, U12.P5, U12.P7
GND12: C13.2, J37.1, J39.1, LED12.1, TP52.1, U13.P5, U13.P7
GND13: C14.2, J40.1, J42.1, LED13.1, TP56.1, U14.P5, U14.P7
GND14: C15.2, J43.1, J45.1, LED14.1, TP60.1, U15.P5, U15.P7
GND15: C16.2, J46.1, J48.1, LED15.1, TP64.1, U16.P5, U16.P7
GND16: C17.2, J49.1, J51.1, LED16.1, TP68.1, U17.P5, U17.P7
GND17: C18.2, J52.1, J54.1, LED17.1, TP72.1, U18.P5, U18.P7
GND18: C19.2, J55.1, J57.1, LED18.1, TP76.1, U19.P5, U19.P7
GND19: C20.2, J58.1, J60.1, LED19.1, TP80.1, U20.P5, U20.P7
GND20: C21.2, J61.1, J63.1, LED20.1, TP84.1, U21.P5, U21.P7
GND21: C22.2, J64.1, J66.1, LED21.1, TP88.1, U22.P5, U22.P7
GND22: C23.2, J67.1, J69.1, LED22.1, TP92.1, U23.P5, U23.P7
GND23: C24.2, J70.1, J72.1, LED23.1, TP96.1, U24.P5, U24.P7
GND24: C25.2, J73.1, J75.1, LED24.1, TP100.1, U25.P5, U25.P7
GND25: C26.2, J76.1, J78.1, LED25.1, TP104.1, U26.P5, U26.P7
GND26: C27.2, J79.1, J81.1, LED26.1, TP108.1, U27.P5, U27.P7
GND27: C28.2, J82.1, J84.1, LED27.1, TP112.1, U28.P5, U28.P7
GND28: C29.2, J85.1, J87.1, LED28.1, TP116.1, U29.P5, U29.P7
GND29: C30.2, J88.1, J90.1, LED29.1, TP120.1, U30.P5, U30.P7
GND30: C31.2, J91.1, J93.1, LED30.1, TP124.1, U31.P5, U31.P7
GND31: C32.2, J94.1, J96.1, LED31.1, TP128.1, U32.P5, U32.P7
GND32: C33.2, J97.1, J99.1, LED32.1, TP132.1, U33.P5, U33.P7
GND33: C34.2, J100.1, J102.1, LED33.1, TP136.1, U34.P5, U34.P7
GND34: C35.2, J103.1, J105.1, LED34.1, TP140.1, U35.P5, U35.P7
GND35: C36.2, J106.1, J108.1, LED35.1, TP144.1, U36.P5, U36.P7
GND36: C37.2, J109.1, J111.1, LED36.1, TP148.1, U37.P5, U37.P7
GND37: C38.2, J112.1, J114.1, LED37.1, TP152.1, U38.P5, U38.P7
GND38: C39.2, J115.1, J117.1, LED38.1, TP156.1, U39.P5, U39.P7
GND39: C40.2, J118.1, J120.1, LED39.1, TP160.1, U40.P5, U40.P7
GND40: C41.2, J121.1, J123.1, LED40.1, TP164.1, U41.P5, U41.P7
GND41: C42.2, J124.1, J126.1, LED41.1, TP168.1, U42.P5, U42.P7
GND42: C43.2, J127.1, J129.1, LED42.1, TP172.1, U43.P5, U43.P7
GND43: C44.2, J130.1, J132.1, LED43.1, TP176.1, U44.P5, U44.P7
GND44: C45.2, J133.1, J135.1, LED44.1, TP180.1, U45.P5, U45.P7
GND45: C46.2, J136.1, J138.1, LED45.1, TP184.1, U46.P5, U46.P7
GND46: C47.2, J139.1, J141.1, LED46.1, TP188.1, U47.P5, U47.P7
GND47: C48.2, J142.1, J144.1, LED47.1, TP192.1, U48.P5, U48.P7
GND48: C49.2, J145.1, J147.1, LED48.1, TP196.1, U49.P5, U49.P7
GND49: C50.2, J148.1, J150.1, LED49.1, TP200.1, U50.P5, U50.P7
GND50: C51.2, J151.1, J153.1, LED50.1, TP204.1, U51.P5, U51.P7
GND51: C52.2, J154.1, J156.1, LED51.1, TP208.1, U52.P5, U52.P7
GND52: C53.2, J157.1, J159.1, LED52.1, TP212.1, U53.P5, U53.P7
GND53: C54.2, J160.1, J162.1, LED53.1, TP216.1, U54.P5, U54.P7
GND54: C55.2, J163.1, J165.1, LED54.1, TP220.1, U55.P5, U55.P7
GND55: C56.2, J166.1, J168.1, LED55.1, TP224.1, U56.P5, U56.P7
GND56: C57.2, J169.1, J171.1, LED56.1, TP228.1, U57.P5, U57.P7
GND57: C58.2, J172.1, J174.1, LED57.1, TP232.1, U58.P5, U58.P7
GND58: C59.2, J175.1, J177.1, LED58.1, TP236.1, U59.P5, U59.P7
GND59: C60.2, J178.1, J180.1, LED59.1, TP240.1, U60.P5, U60.P7
GND60: C61.2, J181.1, J183.1, LED60.1, TP244.1, U61.P5, U61.P7
GND61: C62.2, J184.1, J186.1, LED61.1, TP248.1, U62.P5, U62.P7
GND62: C63.2, J187.1, J189.1, LED62.1, TP252.1, U63.P5, U63.P7
GND63: C64.2, J190.1, J192.1, LED63.1, TP256.1, U64.P5, U64.P7
unnamed: ADDR.3, R5.1
unnamed: D1.A, R4.1
unnamed: D1.C, LED.2
unnamed: I2C_PU1.1, R6.2
unnamed: I2C_PU.1, R1.2
unnamed: I2C_PU.3, R2.2
unnamed: I2C_PU1.3, R7.2
unnamed: D2.A, R8.1
unnamed: D2.C, LED1.2
unnamed: ADDR1.3, R10.1
unnamed: I2C_PU2.1, R11.2
unnamed: I2C_PU2.3, R12.2
unnamed: D3.A, R13.1
unnamed: D3.C, LED2.2
unnamed: ADDR2.3, R15.1
unnamed: I2C_PU3.1, R16.2
unnamed: I2C_PU3.3, R17.2
unnamed: D4.A, R18.1
unnamed: D4.C, LED3.2
unnamed: ADDR3.3, R20.1
unnamed: I2C_PU4.1, R21.2
unnamed: I2C_PU4.3, R22.2
unnamed: D5.A, R23.1
unnamed: D5.C, LED4.2
unnamed: ADDR4.3, R25.1
unnamed: I2C_PU5.1, R26.2
unnamed: I2C_PU5.3, R27.2
unnamed: D6.A, R28.1
unnamed: D6.C, LED5.2
unnamed: ADDR5.3, R30.1
unnamed: I2C_PU6.1, R31.2
unnamed: I2C_PU6.3, R32.2
unnamed: D7.A, R33.1
unnamed: D7.C, LED6.2
unnamed: ADDR6.3, R35.1
unnamed: I2C_PU7.1, R36.2
unnamed: I2C_PU7.3, R37.2
unnamed: D8.A, R38.1
unnamed: D8.C, LED7.2
unnamed: ADDR7.3, R40.1
unnamed: I2C_PU8.1, R41.2
unnamed: I2C_PU8.3, R42.2
unnamed: D9.A, R43.1
unnamed: D9.C, LED8.2
unnamed: ADDR8.3, R45.1
unnamed: I2C_PU9.1, R46.2
unnamed: I2C_PU9.3, R47.2
unnamed: D10.A, R48.1
unnamed: D10.C, LED9.2
unnamed: ADDR9.3, R50.1
unnamed: I2C_PU10.1, R51.2
unnamed: I2C_PU10.3, R52.2
unnamed: D11.A, R53.1
unnamed: D11.C, LED10.2
unnamed: ADDR10.3, R55.1
unnamed: I2C_PU11.1, R56.2
unnamed: I2C_PU11.3, R57.2
unnamed: D12.A, R58.1
unnamed: D12.C, LED11.2
unnamed: ADDR11.3, R60.1
unnamed: I2C_PU12.1, R61.2
unnamed: I2C_PU12.3, R62.2
unnamed: D13.A, R63.1
unnamed: D13.C, LED12.2
unnamed: ADDR12.3, R65.1
unnamed: I2C_PU13.1, R66.2
unnamed: I2C_PU13.3, R67.2
unnamed: D14.A, R68.1
unnamed: D14.C, LED13.2
unnamed: ADDR13.3, R70.1
unnamed: I2C_PU14.1, R71.2
unnamed: I2C_PU14.3, R72.2
unnamed: D15.A, R73.1
unnamed: D15.C, LED14.2
unnamed: ADDR14.3, R75.1
unnamed: I2C_PU15.1, R76.2
unnamed: I2C_PU15.3, R77.2
unnamed: D16.A, R78.1
unnamed: D16.C, LED15.2
unnamed: ADDR15.3, R80.1
unnamed: I2C_PU16.1, R81.2
unnamed: I2C_PU16.3, R82.2
unnamed: D17.A, R83.1
unnamed: D17.C, LED16.2
unnamed: ADDR16.3, R85.1
unnamed: I2C_PU17.1, R86.2
unnamed: I2C_PU17.3, R87.2
unnamed: D18.A, R88.1
unnamed: D18.C, LED17.2
unnamed: ADDR17.3, R90.1
unnamed: I2C_PU18.1, R91.2
unnamed: I2C_PU18.3, R92.2
unnamed: D19.A, R93.1
unnamed: D19.C, LED18.2
unnamed: ADDR18.3, R95.1
unnamed: I2C_PU19.1, R96.2
unnamed: I2C_PU19.3, R97.2
unnamed: D20.A, R98.1
unnamed: D20.C, LED19.2
unnamed: ADDR19.3, R100.1
unnamed: I2C_PU20.1, R101.2
unnamed: I2C_PU20.3, R102.2
unnamed: D21.A, R103.1
unnamed: D21.C, LED20.2
unnamed: ADDR20.3, R105.1
unnamed: I2C_PU21.1, R106.2
unnamed: I2C_PU21.3, R107.2
unnamed: D22.A, R108.1
unnamed: D22.C, LED21.2
unnamed: ADDR21.3, R110.1
unnamed: I2C_PU22.1, R111.2
unnamed: I2C_PU22.3, R112.2
unnamed: D23.A, R113.1
unnamed: D23.C, LED22.2
unnamed: ADDR22.3, R115.1
unnamed: I2C_PU23.1, R116.2
unnamed: I2C_PU23.3, R117.2
unnamed: D24.A, R118.1
unnamed: D24.C, LED23.2
unnamed: ADDR23.3, R120.1
unnamed: I2C_PU24.1, R121.2
unnamed: I2C_PU24.3, R122.2
unnamed: D25.A, R123.1
unnamed: D25.C, LED24.2
unnamed: ADDR24.3, R125.1
unnamed: I2C_PU25.1, R126.2
unnamed: I2C_PU25.3, R127.2
unnamed: D26.A, R128.1
unnamed: D26.C, LED25.2
unnamed: ADDR25.3, R130.1
unnamed: I2C_PU26.1, R131.2
unnamed: I2C_PU26.3, R132.2
unnamed: D27.A, R133.1
unnamed: D27.C, LED26.2
unnamed: ADDR26.3, R135.1
unnamed: I2C_PU27.1, R136.2
unnamed: I2C_PU27.3, R137.2
unnamed: D28.A, R138.1
unnamed: D28.C, LED27.2
unnamed: ADDR27.3, R140.1
unnamed: I2C_PU28.1, R141.2
unnamed: I2C_PU28.3, R142.2
unnamed: D29.A, R143.1
unnamed: D29.C, LED28.2
unnamed: ADDR28.3, R145.1
unnamed: I2C_PU29.1, R146.2
unnamed: I2C_PU29.3, R147.2
unnamed: D30.A, R148.1
unnamed: D30.C, LED29.2
unnamed: ADDR29.3, R150.1
unnamed: I2C_PU30.1, R151.2
unnamed: I2C_PU30.3, R152.2
unnamed: D31.A, R153.1
unnamed: D31.C, LED30.2
unnamed: ADDR30.3, R155.1
unnamed: I2C_PU31.1, R156.2
unnamed: I2C_PU31.3, R157.2
unnamed: D32.A, R158.1
unnamed: D32.C, LED31.2
unnamed: ADDR31.3, R160.1
unnamed: I2C_PU32.1, R161.2
unnamed: I2C_PU32.3, R162.2
unnamed: D33.A, R163.1
unnamed: D33.C, LED32.2
unnamed: ADDR32.3, R165.1
unnamed: I2C_PU33.1, R166.2
unnamed: I2C_PU33.3, R167.2
unnamed: D34.A, R168.1
unnamed: D34.C, LED33.2
unnamed: ADDR33.3, R170.1
unnamed: I2C_PU34.1, R171.2
unnamed: I2C_PU34.3, R172.2
unnamed: D35.A, R173.1
unnamed: D35.C, LED34.2
unnamed: ADDR34.3, R175.1
unnamed: I2C_PU35.1, R176.2
unnamed: I2C_PU35.3, R177.2
unnamed: D36.A, R178.1
unnamed: D36.C, LED35.2
unnamed: ADDR35.3, R180.1
unnamed: I2C_PU36.1, R181.2
unnamed: I2C_PU36.3, R182.2
unnamed: D37.A, R183.1
unnamed: D37.C, LED36.2
unnamed: ADDR36.3, R185.1
unnamed: I2C_PU37.1, R186.2
unnamed: I2C_PU37.3, R187.2
unnamed: D38.A, R188.1
unnamed: D38.C, LED37.2
unnamed: ADDR37.3, R190.1
unnamed: I2C_PU38.1, R191.2
unnamed: I2C_PU38.3, R192.2
unnamed: D39.A, R193.1
unnamed: D39.C, LED38.2
unnamed: ADDR38.3, R195.1
unnamed: I2C_PU39.1, R196.2
unnamed: I2C_PU39.3, R197.2
unnamed: D40.A, R198.1
unnamed: D40.C, LED39.2
unnamed: ADDR39.3, R200.1
unnamed: I2C_PU40.1, R201.2
unnamed: I2C_PU40.3, R202.2
unnamed: D41.A, R203.1
unnamed: D41.C, LED40.2
unnamed: ADDR40.3, R205.1
unnamed: I2C_PU41.1, R206.2
unnamed: I2C_PU41.3, R207.2
unnamed: D42.A, R208.1
unnamed: D42.C, LED41.2
unnamed: ADDR41.3, R210.1
unnamed: I2C_PU42.1, R211.2
unnamed: I2C_PU42.3, R212.2
unnamed: D43.A, R213.1
unnamed: D43.C, LED42.2
unnamed: ADDR42.3, R215.1
unnamed: I2C_PU43.1, R216.2
unnamed: I2C_PU43.3, R217.2
unnamed: D44.A, R218.1
unnamed: D44.C, LED43.2
unnamed: ADDR43.3, R220.1
unnamed: I2C_PU44.1, R221.2
unnamed: I2C_PU44.3, R222.2
unnamed: D45.A, R223.1
unnamed: D45.C, LED44.2
unnamed: ADDR44.3, R225.1
unnamed: I2C_PU45.1, R226.2
unnamed: I2C_PU45.3, R227.2
unnamed: D46.A, R228.1
unnamed: D46.C, LED45.2
unnamed: ADDR45.3, R230.1
unnamed: I2C_PU46.1, R231.2
unnamed: I2C_PU46.3, R232.2
unnamed: D47.A, R233.1
unnamed: D47.C, LED46.2
unnamed: ADDR46.3, R235.1
unnamed: I2C_PU47.1, R236.2
unnamed: I2C_PU47.3, R237.2
unnamed: D48.A, R238.1
unnamed: D48.C, LED47.2
unnamed: ADDR47.3, R240.1
unnamed: I2C_PU48.1, R241.2
unnamed: I2C_PU48.3, R242.2
unnamed: D49.A, R243.1
unnamed: D49.C, LED48.2
unnamed: ADDR48.3, R245.1
unnamed: I2C_PU49.1, R246.2
unnamed: I2C_PU49.3, R247.2
unnamed: D50.A, R248.1
unnamed: D50.C, LED49.2
unnamed: ADDR49.3, R250.1
unnamed: I2C_PU50.1, R251.2
unnamed: I2C_PU50.3, R252.2
unnamed: D51.A, R253.1
unnamed: D51.C, LED50.2
unnamed: ADDR50.3, R255.1
unnamed: I2C_PU51.1, R256.2
unnamed: I2C_PU51.3, R257.2
unnamed: D52.A, R258.1
unnamed: D52.C, LED51.2
unnamed: ADDR51.3, R260.1
unnamed: I2C_PU52.1, R261.2
unnamed: I2C_PU52.3, R262.2
unnamed: D53.A, R263.1
unnamed: D53.C, LED52.2
unnamed: ADDR52.3, R265.1
unnamed: I2C_PU53.1, R266.2
unnamed: I2C_PU53.3, R267.2
unnamed: D54.A, R268.1
unnamed: D54.C, LED53.2
unnamed: ADDR53.3, R270.1
unnamed: I2C_PU54.1, R271.2
unnamed: I2C_PU54.3, R272.2
unnamed: D55.A, R273.1
unnamed: D55.C, LED54.2
unnamed: ADDR54.3, R275.1
unnamed: I2C_PU55.1, R276.2
unnamed: I2C_PU55.3, R277.2
unnamed: D56.A, R278.1
unnamed: D56.C, LED55.2
unnamed: ADDR55.3, R280.1
unnamed: I2C_PU56.1, R281.2
unnamed: I2C_PU56.3, R282.2
unnamed: D57.A, R283.1
unnamed: D57.C, LED56.2
unnamed: ADDR56.3, R285.1
unnamed: I2C_PU57.1, R286.2
unnamed: I2C_PU57.3, R287.2
unnamed: D58.A, R288.1
unnamed: D58.C, LED57.2
unnamed: ADDR57.3, R290.1
unnamed: I2C_PU58.1, R291.2
unnamed: I2C_PU58.3, R292.2
unnamed: D59.A, R293.1
unnamed: D59.C, LED58.2
unnamed: ADDR58.3, R295.1
unnamed: I2C_PU59.1, R296.2
unnamed: I2C_PU59.3, R297.2
unnamed: D60.A, R298.1
unnamed: D60.C, LED59.2
unnamed: ADDR59.3, R300.1
unnamed: I2C_PU60.1, R301.2
unnamed: I2C_PU60.3, R302.2
unnamed: D61.A, R303.1
unnamed: D61.C, LED60.2
unnamed: ADDR60.3, R305.1
unnamed: I2C_PU61.1, R306.2
unnamed: I2C_PU61.3, R307.2
unnamed: D62.A, R308.1
unnamed: D62.C, LED61.2
unnamed: ADDR61.3, R310.1
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
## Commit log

2022-11-02 Removes ADDR pin from header
    * Routes board
2022-11-02 Adds tkeepout to temperature sensor
2022-11-02 Adds silk
2022-11-02 Adds decoupling cap which resulted in additional routing
2022-11-02 Adds Qwiic Micro shell of a design
    * Adds folders for hardware files
2022-11-03 Routes Micro, adds silk
2022-11-03 Adds note for default addresses
2022-11-04 Fixes off center footprint, adds center pad on temp sensor to ground
    *
2022-11-04 Adds alternative board with exposed copper on the underside
2022-11-04 Removes alternate version
2022-11-04 Moves OSHW logo, approves various DRC errors, moves silk
2022-11-04 Moves address jumper for better symmetry
2022-11-04 Adds a single, incredibly important via
2022-11-04 re-adds the missing tstop to the temperature sensor
2022-11-04 Updates temp sensor footprint, Adds bstop underneath IC
    * Adds via directly underneath sensor for better temperature sensing
    * Fixes various routing inconsistencies
2022-11-04 Fixes units overlap text with design by text
2022-11-04 Moves address selection around to be more clear in the schematic
    * Changes second address option on micro to 3v3 instead of GND
2022-11-04 Updates address selection text in schematic to be more clear
2022-11-04 Adds the "u" in temperature
2022-11-04 Updates temp sensor footprint to have reduced pasted on center pad
2022-11-07 Adds default address text
2022-11-07 Adds production files for Qwiic version
2022-11-07 Adds Production files for Qwiic Micro
2022-11-07 Re-panelizes Qwiic Micro
2022-11-09 Adds new Qwiic Micro panel
2022-11-09 Moves qwiic micro panel to production folder
2022-11-09 Renames panel to to include version number
2022-11-29 Replaces r7 with a 57.6k resistor
2022-11-29 Adds 56k to R7
2023-01-26 Initial Github io page checkin
    Docs branch
2023-01-31 Adding light/dark mode and fixing action shot for ex 2
    Adding light/dark mode and fixing action shot for ex 2
2023-02-08 Updates to add PrintToPDF
    Added PrintToPDF, updated support page, fixed a few images
2023-02-08 Adding with-pdf to .github workflow and fixing links
2023-02-08 Changing versions of checkout and python to 3
2023-02-08 Fix badge link
2023-02-14 Fixing link to pdf
2023-02-14 Cleaning up pdf images and titles
2023-02-15 Adding video centering and cleaning up overview
2023-02-15 Updating fav icon
2023-02-15 Deployed f3d33dd with MkDocs version: 1.4.2
